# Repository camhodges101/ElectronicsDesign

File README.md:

## Electronics Design
Raspberry Pi and STM32 with sensors and interfaces on a single PCB

The purpose of this project is to create a single custom PCB design including a Raspberry Pi CM4, STM32 Micro controller, 6 axis single chip IMU, CAN datalink and supporting power supplies. 

This is intended to be a general purpose controller or datalogger. The STM32 allows for high speed IO tasks while the CM4 supports more complex computations and remote access using something like AWS GreenGrass.

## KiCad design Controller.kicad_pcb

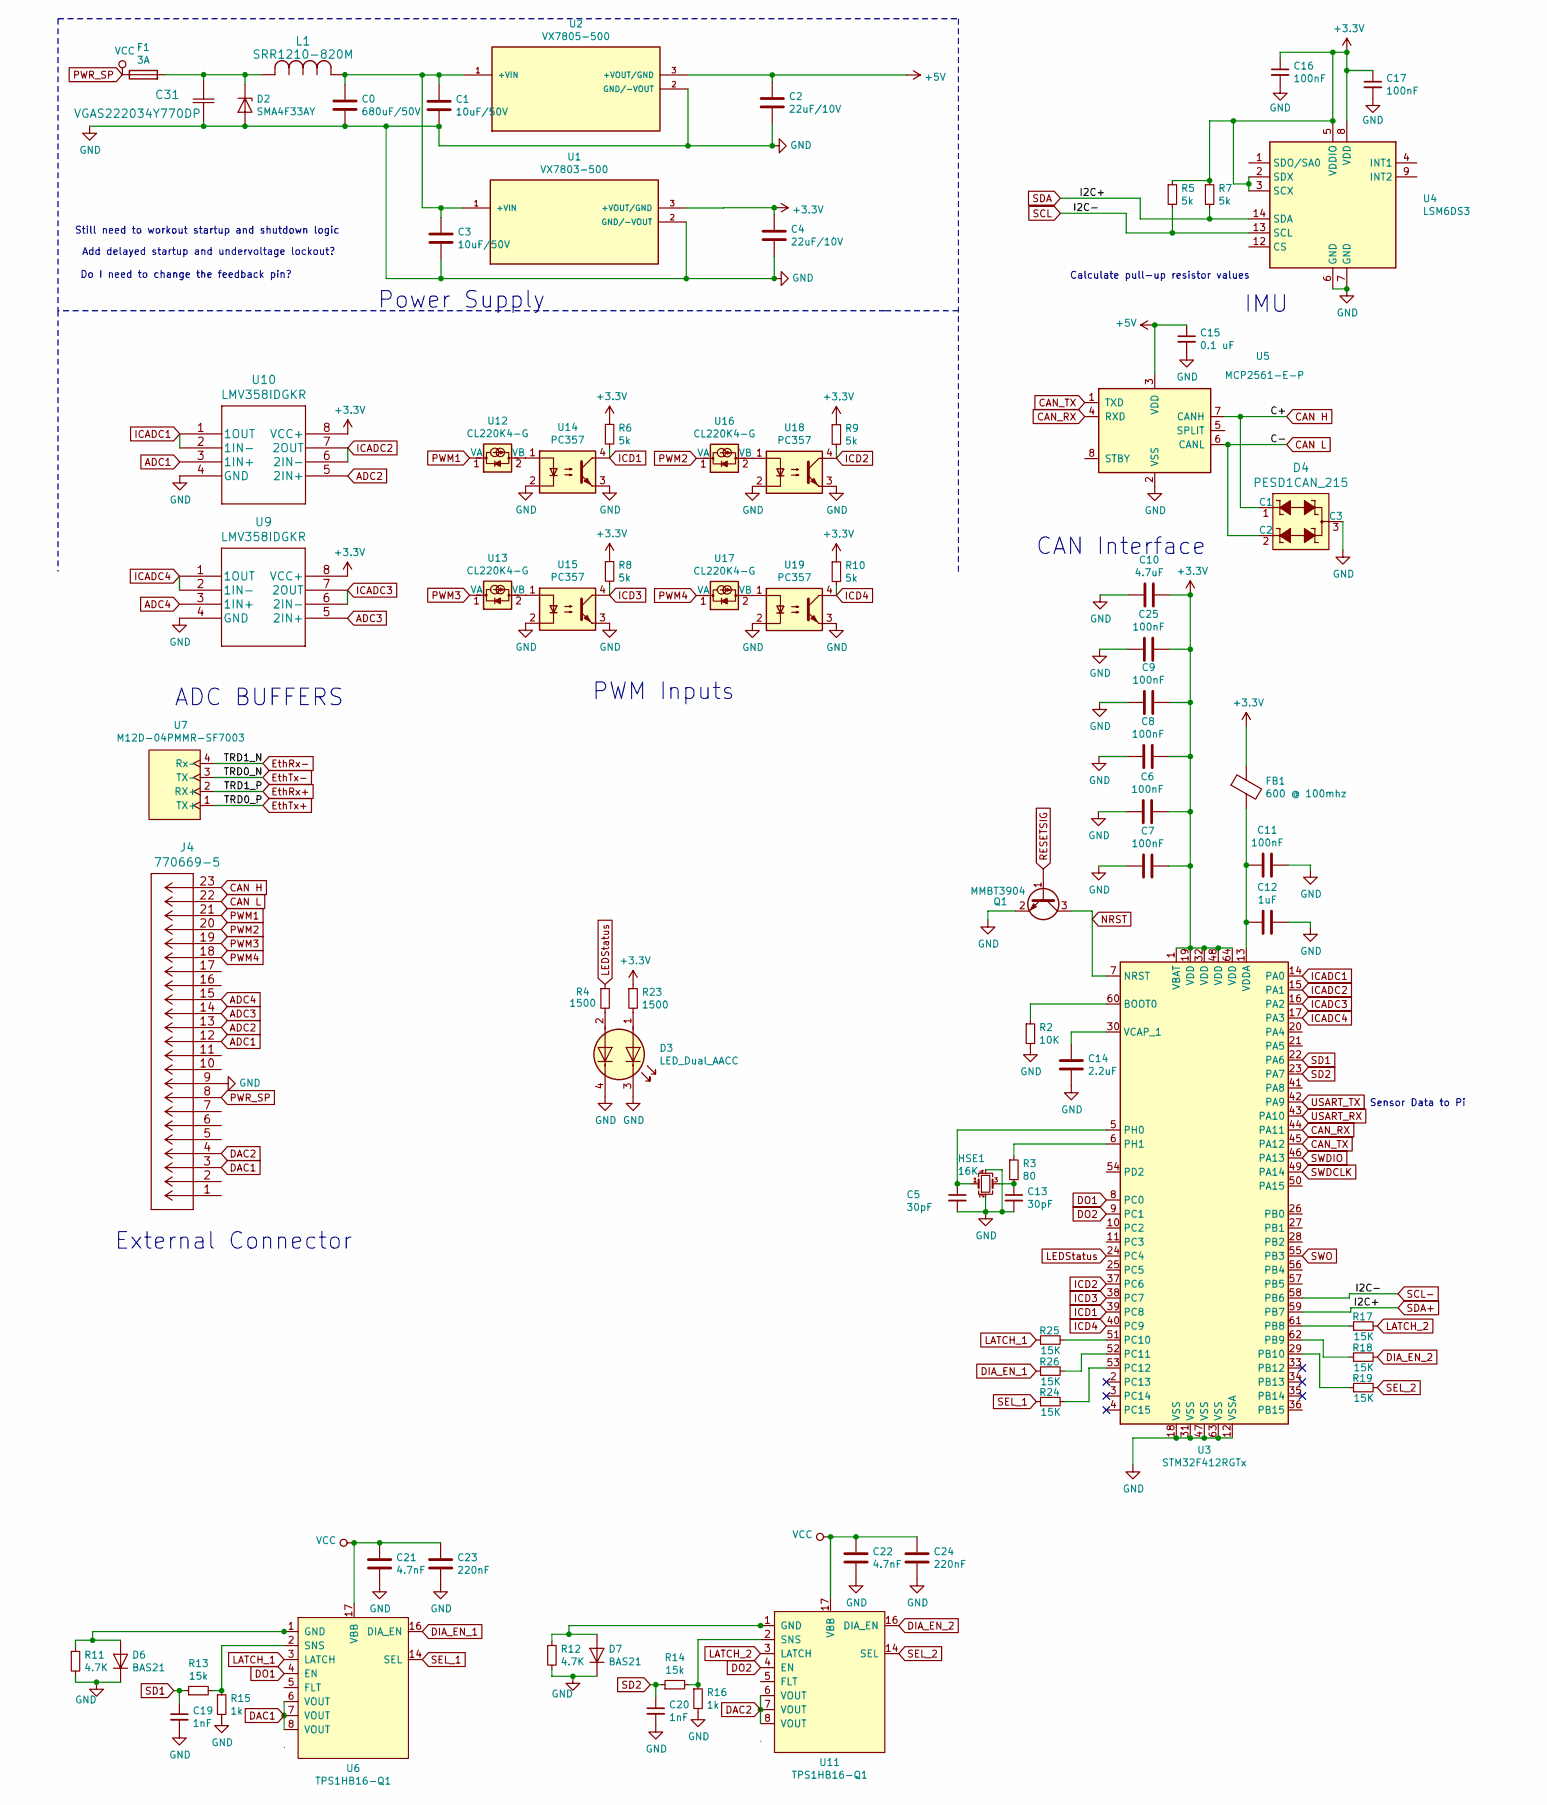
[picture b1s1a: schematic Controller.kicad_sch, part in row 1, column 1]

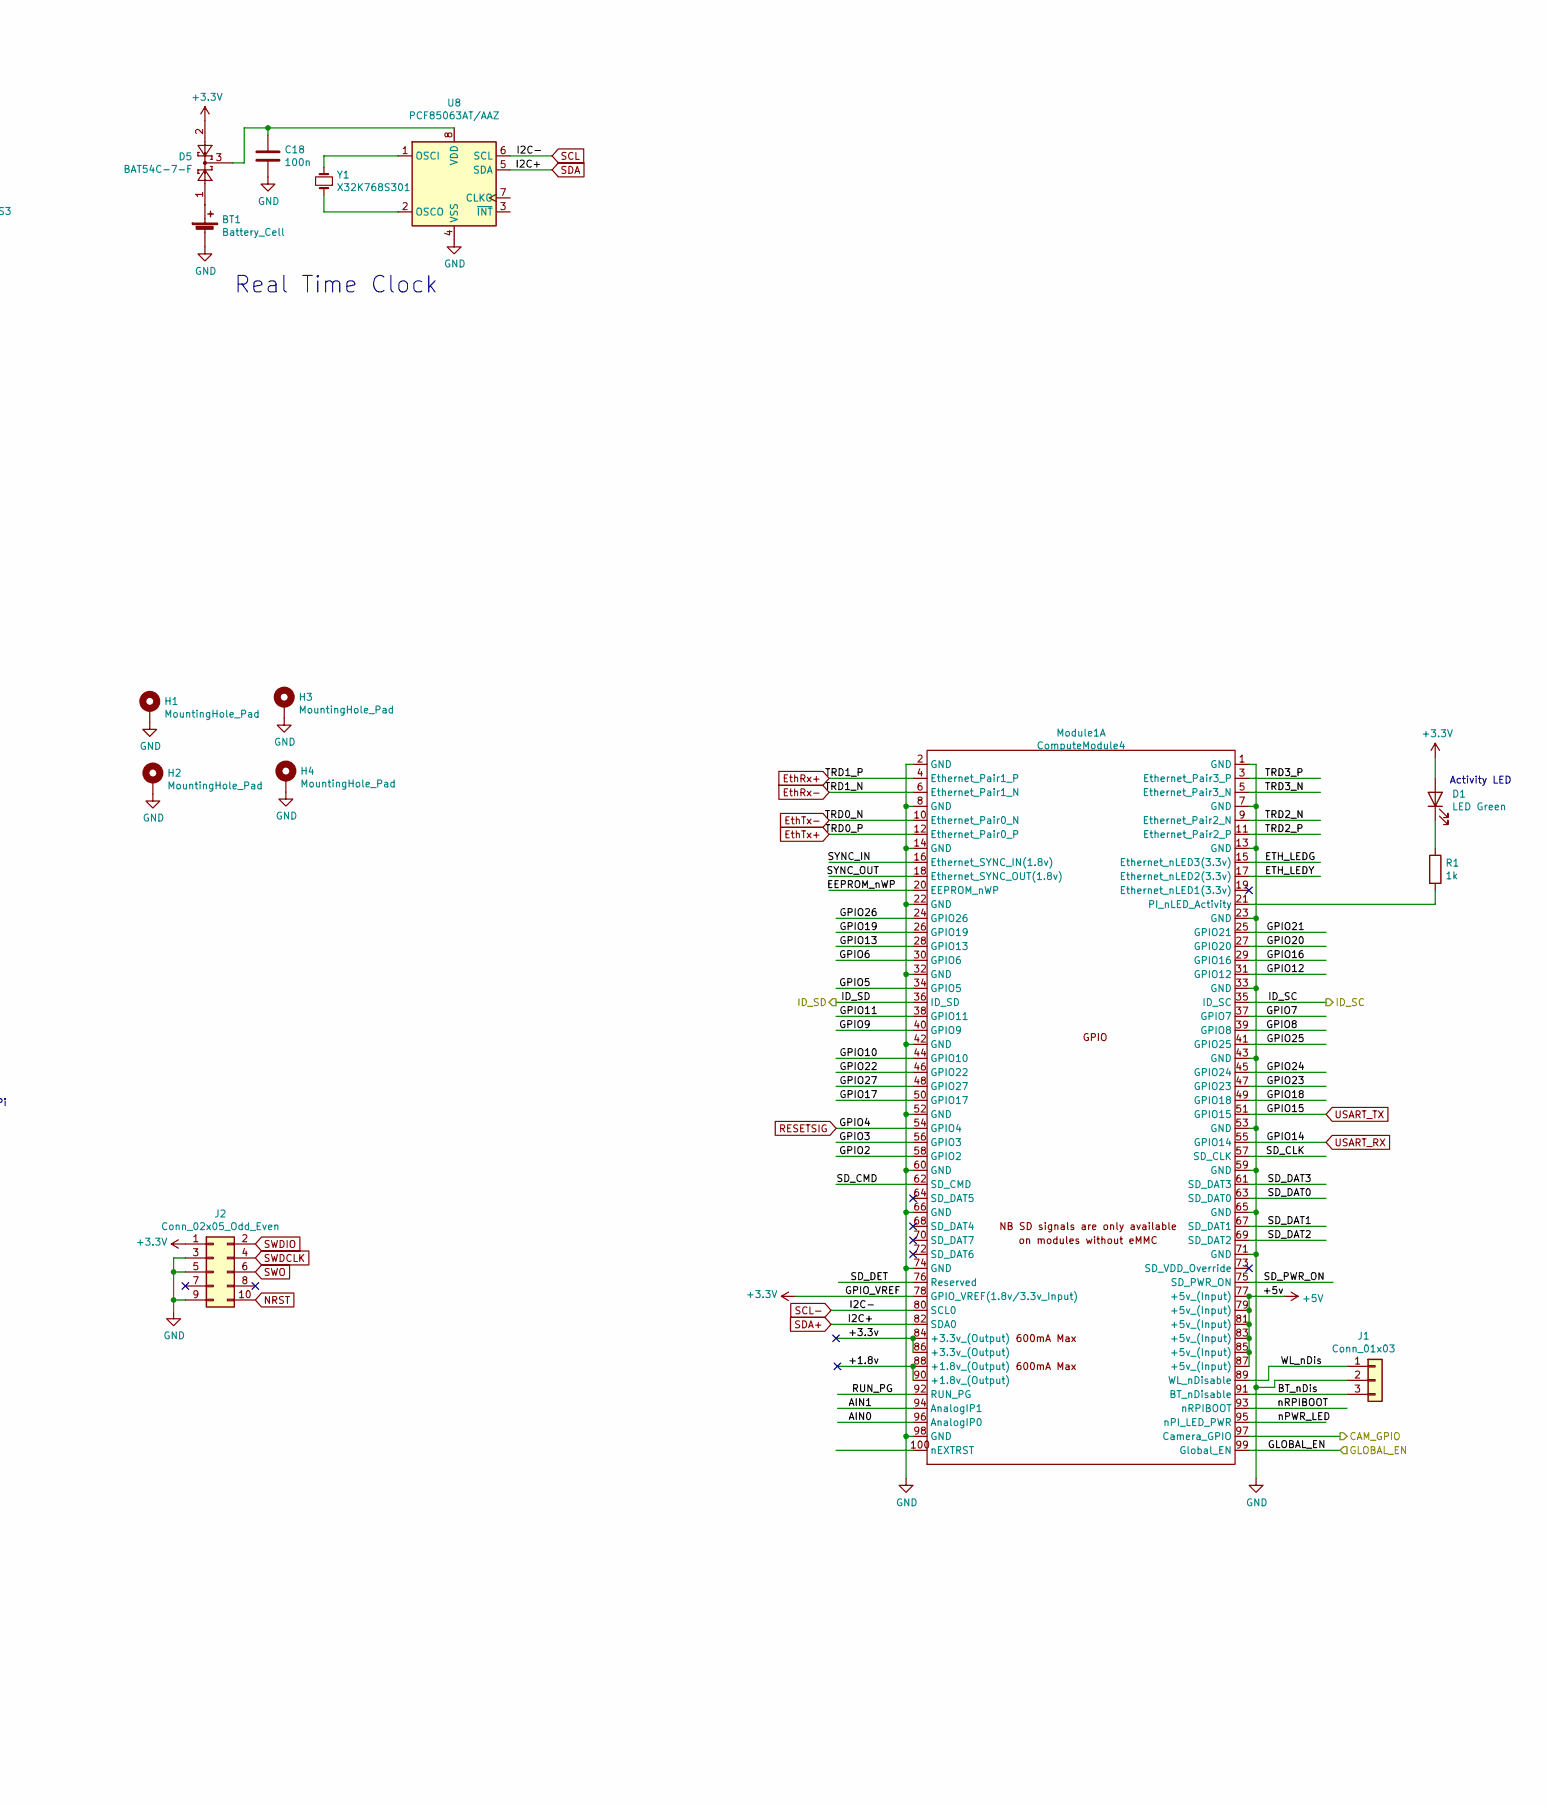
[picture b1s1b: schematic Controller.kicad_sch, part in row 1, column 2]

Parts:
BT1: Battery_Cell; BatteryHolder_Keystone_3034_1x20mm; Part Description Battery Retainer Coin, 20.0mm 1 Cell SM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
C0: 680uF/50V; UPM1H681MHD6TN; Part No. UPM1H681MHD6TN
C1, C3: 10uF/50V; CAPC3216X140N; Part No. CL31B106KBHNNNE
C2, C4: 22uF/10V; CAPC2012X140N; Part No. CL21A226KPCLRNC
C5, C13: 30pF; C0805C300J5GACTU; Part No. C0805C300J5GACTU
C6, C7, C8, C9, C11, C16, C17, C25: 100nF; CAPC2012X94N; Part No. C0805X475J8RAC7800
C10: 4.7uF; CAPC2012X145N; Part No. C0805X475J8RAC7800
C12: 1uF; C0603C105K8PACTU; Part No. C0603C105K8PACTU
C14: 2.2uF; C0805C225K8RACTU; Part No. C0805C225K8RACTU
C15: 0.1 uF; CAPC2012X88N; Part No. C0805C101J5GACTU
C18: 100n; CAPC2012X94N; Part No. C0805X475J8RAC7800
C19, C20: 1nF; C0805C102J5HAC7800; Part No. C0805C102J5HAC7800
C21, C22: 4.7nF; CAPC2012X145N; Part No. C0805X475J8RAC7800
C23, C24: 220nF; CAPC2012X140N
C31: VGAS222034Y770DP
D1: LED Green; LED_0603_1608Metric; Part Description Green 572nm LED Indication - Discrete 2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
D2: SMA4F33AY; Part No. SMA4F33AY
D3: LED_Dual_AACC; APHBM2012SURKZGKC
D4: PESD1CAN_215; SOT-23-3; MPN PESD1CAN,215; Digi-Key_PN 1727-3817-1-ND
D5: BAT54C-7-F; SOT-23; Part Description Diode Array 1 Pair Common Cathode Schot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
D6, D7: BAS21; Part No. BAS21LT3G
F1: 3A; 65800001109; Part No. 65800001109
FB1: 600 @ 100mhz; BEADC2012X110N; Part No. 742792040
H1, H2, H3, H4: MountingHole_Pad
HSE1: 16K; XTAL_ECS-160-12-33Q-JES-TR; Part No. ECS-160-12-33Q-JES-TR
J1: Conn_01x03; PinHeader_1x03_P2.54mm_Vertical; Part Description 3pin 0.1" connector
J2: Conn_02x05_Odd_Even; 10056844-110ALF; Part No. 10056844-110ALF
J4: 770669-5
L1: SRR1210-820M
Module1: ComputeModule4; Raspberry-Pi-4-Compute-Module; Part Description 100 Position Connector Receptacle, Cent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
Q1: MMBT3904; SOT-23
R1: 1k; R_0402_1005Metric; Part Description Resistor 1K M1005 1% 63mW
R2: 10K; RESC2012X60N; Part No. RC0805JR-0710KL
R3: 80; RESC2012X60N; PArt No. RC0805JR-0782RL
R4, R23: 1500; RESC2012X60N; Part No. AC0805JR-07150RL
R5, R6, R7, R8, R9, R10: 5k; RESC2012X60N
R11, R12: 4.7K; RESC2012X60N; Part No. RC0805JR-074K7L
R13, R14: 15k; RESC2012X60N; Part No. RC0805FR-0715KL
R15, R16: 1k; RESC2012X60N; Part No. RC0805JR-071KL
R17, R18, R19, R24, R25, R26: 15K; RESC2012X60N; Part No. RC0805JR-0715KL
U1: VX7803-500; VX78012-500_VX7803-500; PARTREV 1.0
U2: VX7805-500; VX78012-500_VX7805-500; PARTREV 1.0
U3: STM32F412RGTx; LQFP-64_10x10mm_P0.5mm
U4: LSM6DS3; LGA-14_3x2.5mm_P0.5mm_LayoutBorder3x4y
U5: MCP2561-E-P; DIP-8_W7.62mm
U6, U11: TPS1HB16-Q1; SOP65P640X120-17N
U7: M12D-04PMMR-SF7003
U8: PCF85063AT/AAZ; SOIC-8_3.9x4.9mm_P1.27mm; Part Description Real Time Clock (RTC) IC Clock/Calendar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
U9, U10: LMV358IDGKR; Part No. LMV358IDGKR
U12, U13, U16, U17: CL220K4-G; TO-252-2
U14, U15, U18, U19: PC357; PC357N2J000F; Part No. PC357N2J000F
Y1: X32K768S301; Crystal_SMD_3215-2Pin_3.2x1.5mm; Part Description Crystal 32.768KHz 7pF 20pmm

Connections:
+3V3: C4.1, C6.2, C7.2, C8.2, C9.2, C10.2, C16.1, C17.1, C25.2, D1.2 (A), D5.2, FB1.1, J2.1, Module1.78 (GPIO_VREF(1.8v/3.3v_Input)), R5.1, R6.1, R7.1, R8.1, R9.1, R10.1, R23.1, U1.3 (+VOUT/GND), U3.1 (VBAT), U3.19 (VDD), U3.32 (VDD), U3.48 (VDD), U3.64 (VDD), U4.2 (SDX), U4.3 (SCX), U4.5 (VDDIO), U4.8 (VDD), U9.8 (VCC+), U10.8 (VCC+)
+5V: C2.1, C15.1, Module1.77 (+5v_(Input)), Module1.79 (+5v_(Input)), Module1.81 (+5v_(Input)), Module1.83 (+5v_(Input)), Module1.85 (+5v_(Input)), Module1.87 (+5v_(Input)), U2.3 (+VOUT/GND), U5.3 (VDD)
/+1.8v: Module1.88 (+1.8v_(Output)), Module1.90 (+1.8v_(Output))
/+3.3v: Module1.84 (+3.3v_(Output)), Module1.86 (+3.3v_(Output))
/AIN0: Module1.96 (AnalogIP0)
/AIN1: Module1.94 (AnalogIP1)
/BT_nDis: J1.3, Module1.91 (BT_nDisable)
/CAM_GPIO: Module1.97 (Camera_GPIO)
/EEPROM_nWP: Module1.20 (EEPROM_nWP)
/ETH_LEDG: Module1.15 (Ethernet_nLED3(3.3v))
/ETH_LEDY: Module1.17 (Ethernet_nLED2(3.3v))
/GLOBAL_EN: Module1.99 (Global_EN)
/GPIO2: Module1.58 (GPIO2)
/GPIO3: Module1.56 (GPIO3)
/GPIO5: Module1.34 (GPIO5)
/GPIO6: Module1.30 (GPIO6)
/GPIO7: Module1.37 (GPIO7)
/GPIO8: Module1.39 (GPIO8)
/GPIO9: Module1.40 (GPIO9)
/GPIO10: Module1.44 (GPIO10)
/GPIO11: Module1.38 (GPIO11)
/GPIO12: Module1.31 (GPIO12)
/GPIO13: Module1.28 (GPIO13)
/GPIO16: Module1.29 (GPIO16)
/GPIO17: Module1.50 (GPIO17)
/GPIO18: Module1.49 (GPIO18)
/GPIO19: Module1.26 (GPIO19)
/GPIO20: Module1.27 (GPIO20)
/GPIO21: Module1.25 (GPIO21)
/GPIO22: Module1.46 (GPIO22)
/GPIO23: Module1.47 (GPIO23)
/GPIO24: Module1.45 (GPIO24)
/GPIO25: Module1.41 (GPIO25)
/GPIO26: Module1.24 (GPIO26)
/GPIO27: Module1.48 (GPIO27)
/ID_SC: Module1.35 (ID_SC)
/ID_SD: Module1.36 (ID_SD)
/RUN_PG: Module1.92 (RUN_PG)
/SD_CLK: Module1.57 (SD_CLK)
/SD_CMD: Module1.62 (SD_CMD)
/SD_DAT0: Module1.63 (SD_DAT0)
/SD_DAT1: Module1.67 (SD_DAT1)
/SD_DAT2: Module1.69 (SD_DAT2)
/SD_DAT3: Module1.61 (SD_DAT3)
/SD_DET: Module1.76 (Reserved)
/SD_PWR_ON: Module1.75 (SD_PWR_ON)
/SYNC_IN: Module1.16 (Ethernet_SYNC_IN(1.8v))
/SYNC_OUT: Module1.18 (Ethernet_SYNC_OUT(1.8v))
/TRD2_N: Module1.9 (Ethernet_Pair2_N)
/TRD2_P: Module1.11 (Ethernet_Pair2_P)
/TRD3_N: Module1.5 (Ethernet_Pair3_N)
/TRD3_P: Module1.3 (Ethernet_Pair3_P)
/WL_nDis: J1.1, Module1.89 (WL_nDisable)
/nPWR_LED: Module1.95 (nPI_LED_PWR)
/nRPIBOOT: Module1.93 (nRPIBOOT)
ADC1: J4.12, U10.3 (1IN+)
ADC2: J4.13, U10.5 (2IN+)
ADC3: J4.14, U9.5 (2IN+)
ADC4: J4.15, U9.3 (1IN+)
CAN H: D4.1 (C1), J4.23, U5.7 (CANH)
CAN L: D4.2 (C2), J4.22, U5.6 (CANL)
CAN_RX: U3.44 (PA11), U5.4 (RXD)
CAN_TX: U3.45 (PA12), U5.1 (TXD)
DAC1: J4.3, U6.6 (VOUT), U6.7 (VOUT), U6.8 (VOUT)
DAC2: J4.4, U11.6 (VOUT), U11.7 (VOUT), U11.8 (VOUT)
DIA_EN_1: R26.1, U6.16 (DIA_EN)
DIA_EN_2: R18.2, U11.16 (DIA_EN)
DO1: U3.8 (PC0), U6.4 (EN)
DO2: U3.9 (PC1), U11.4 (EN)
EthRx+: Module1.4 (Ethernet_Pair1_P), U7.2 (RX+)
EthRx-: Module1.6 (Ethernet_Pair1_N), U7.4 (Rx-)
EthTx+: Module1.12 (Ethernet_Pair0_P), U7.1 (TX+)
EthTx-: Module1.10 (Ethernet_Pair0_N), U7.3 (TX-)
GND: BT1.2 (-), C0.2, C1.2, C2.2, C3.2, C4.2, C5.2, C6.1, C7.1, C8.1, C9.1, C10.1, C11.2, C12.2, C13.2, C14.2, C15.2, C16.2, C17.2, C18.2, C19.2, C20.2, C21.2, C22.2, C23.2, C24.2, C25.1, C31.1, D2.2 (A), D3.3 (K1), D3.4 (K2), D4.3 (C3), D6.1 (K), D7.1 (K), H1.1, H2.1, H3.1, H4.1, HSE1.2, HSE1.4, J1.2, J2.3, J2.5, J2.9, J4.9, Module1.1 (GND), Module1.2 (GND), Module1.7 (GND), Module1.8 (GND), Module1.13 (GND), Module1.14 (GND), Module1.22 (GND), Module1.23 (GND), Module1.32 (GND), Module1.33 (GND), Module1.42 (GND), Module1.43 (GND), Module1.52 (GND), Module1.53 (GND), Module1.59 (GND), Module1.60 (GND), Module1.65 (GND), Module1.66 (GND), Module1.71 (GND), Module1.74 (GND), Module1.98 (GND), Q1.2 (E), R2.2, R11.2, R12.2, R15.2, R16.2, U1.2 (GND/-VOUT), U2.2 (GND/-VOUT), U3.12 (VSSA), U3.18 (VSS), U3.31 (VSS), U3.47 (VSS), U3.63 (VSS), U4.6 (GND), U4.7 (GND), U5.2 (VSS), U8.4 (VSS), U9.4 (GND), U10.4 (GND), U14.2, U14.3, U15.2, U15.3, U18.2, U18.3, U19.2, U19.3
ICADC1: U3.14 (PA0), U10.1 (1OUT), U10.2 (1IN-)
ICADC2: U3.15 (PA1), U10.6 (2IN-), U10.7 (2OUT)
ICADC3: U3.16 (PA2), U9.6 (2IN-), U9.7 (2OUT)
ICADC4: U3.17 (PA3), U9.1 (1OUT), U9.2 (1IN-)
ICD1: R6.2, U3.39 (PC8), U14.4
ICD2: R9.2, U3.37 (PC6), U18.4
ICD3: R8.2, U3.38 (PC7), U15.4
ICD4: R10.2, U3.40 (PC9), U19.4
LATCH_1: R25.1, U6.3 (LATCH)
LATCH_2: R17.2, U11.3 (LATCH)
LEDStatus: R4.1, U3.24 (PC4)
NRST: J2.10, Q1.3 (C), U3.7 (NRST)
unnamed: BT1.1 (+), D5.1
unnamed: C0.1, C1.1, C3.1, L1.1, U1.1 (+VIN), U2.1 (+VIN)
unnamed: C5.1, HSE1.1, U3.5 (PH0)
unnamed: C11.1, C12.1, FB1.2, U3.13 (VDDA)
unnamed: C13.1, HSE1.3, R3.2
unnamed: C14.1, U3.30 (VCAP_1)
unnamed: C18.1, D5.3, U8.8 (VDD)
unnamed: C31.2, D2.1 (K), F1.2, L1.2
unnamed: D1.1 (K), R1.1
unnamed: D3.1 (A1), R23.2
unnamed: D3.2 (A2), R4.2
unnamed: D6.2 (A), R11.1, U6.1 (GND)
unnamed: D7.2 (A), R12.1, U11.1 (GND)
unnamed: Module1.21 (PI_nLED_Activity), R1.2
unnamed: R2.1, U3.60 (BOOT0)
unnamed: R3.1, U3.6 (PH1)
unnamed: R13.2, R15.1, U6.2 (SNS)
unnamed: R14.2, R16.1, U11.2 (SNS)
unnamed: R17.1, U3.61 (PB8)
unnamed: R18.1, U3.62 (PB9)
unnamed: R19.1, U3.29 (PB10)
unnamed: R24.2, U3.53 (PC12)
unnamed: R25.2, U3.51 (PC10)
unnamed: R26.2, U3.52 (PC11)
unnamed: U8.1 (OSCI), Y1.2
unnamed: U8.2 (OSCO), Y1.1
unnamed: U12.2 (VB), U14.1
unnamed: U13.2 (VB), U15.1
unnamed: U16.2 (VB), U18.1
unnamed: U17.2 (VB), U19.1
PWM1: J4.21, U12.1 (VA)
PWM2: J4.20, U16.1 (VA)
PWM3: J4.19, U13.1 (VA)
PWM4: J4.18, U17.1 (VA)
PWR_SP: C21.1, C22.1, C23.1, C24.1, F1.1, J4.8, U6.17 (VBB), U11.17 (VBB)
RESETSIG: Module1.54 (GPIO4), Q1.1 (B)
SCL: Module1.80 (SCL0), R5.2, U3.58 (PB6), U4.13 (SCL), U8.6 (SCL)
SD1: C19.1, R13.1, U3.22 (PA6)
SD2: C20.1, R14.1, U3.23 (PA7)
SDA: Module1.82 (SDA0), R7.2, U3.59 (PB7), U4.14 (SDA), U8.5 (SDA)
SEL_1: R24.1, U6.14 (SEL)
SEL_2: R19.2, U11.14 (SEL)
SWDCLK: J2.4, U3.49 (PA14)
SWDIO: J2.2, U3.46 (PA13)
SWO: J2.6, U3.55 (PB3)
USART_RX: Module1.55 (GPIO14), U3.43 (PA10)
USART_TX: Module1.51 (GPIO15), U3.42 (PA9)

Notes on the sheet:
Do I need to change the feedback pin?
Add delayed startup and undervoltage lockout?
Still need to workout startup and shutdown logic
ADC BUFFERS
External Connector
Power Supply
PWM Inputs
CAN Interface
Calculate pull-up resistor values
IMU
Sensor Data to Pi
Real Time Clock
Activity LED

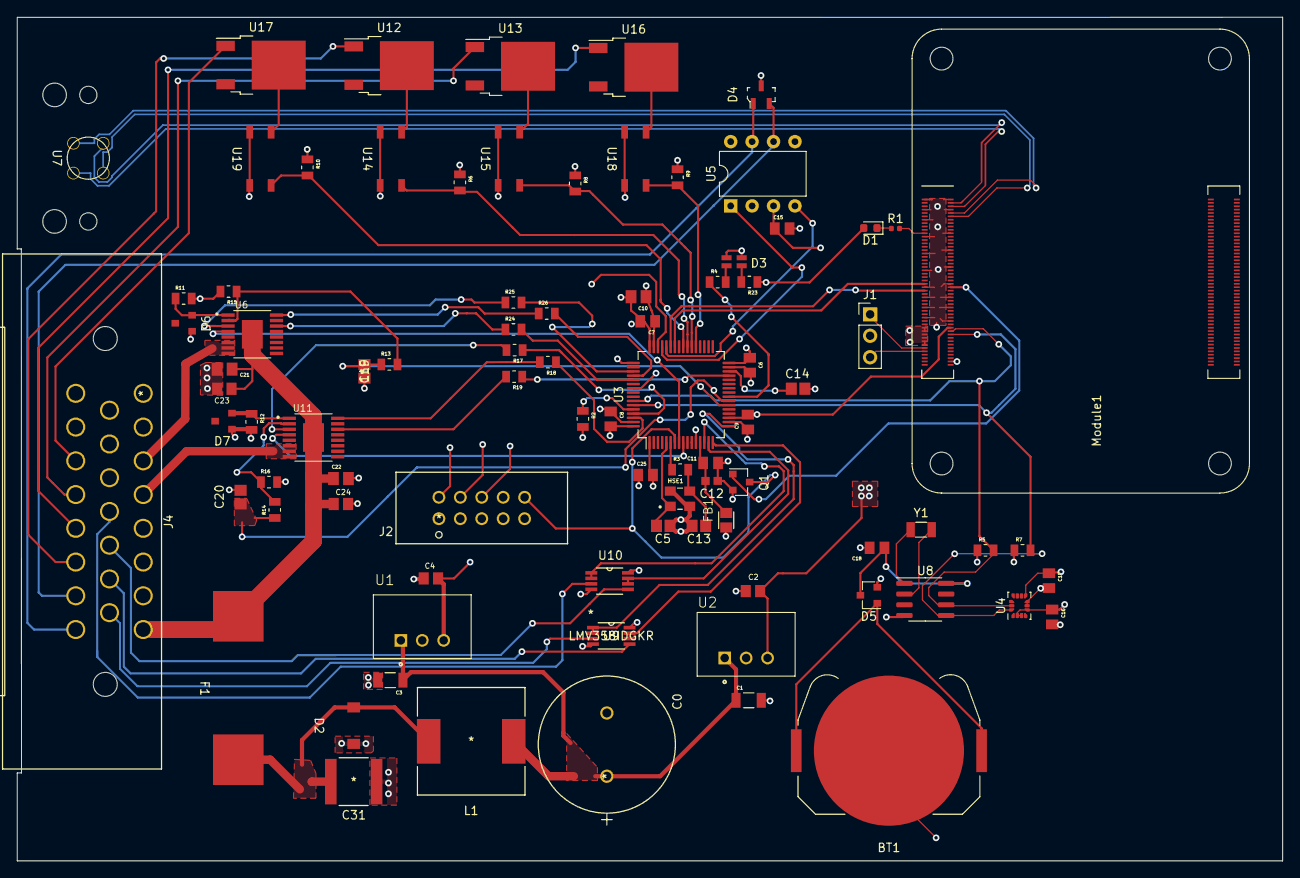
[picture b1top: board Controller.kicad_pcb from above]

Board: 4 copper layers, 150.0 x 100.0 mm, 87 parts (0 on the bottom side), 84 nets.

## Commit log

2021-03-05 firstBuild
2021-03-05 updated Ignore
2021-03-05 removed backups
2021-03-05 includingImages
2021-05-16 Version sent to JLC
2021-05-30 Final images
2021-06-06 pcbimage

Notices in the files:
parts and their libraries:
Copyright 2016 Accelerated Designs. All rights reserved.
